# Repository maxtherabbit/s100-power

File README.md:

# s100-power
PCB for S100 Power Supply which fits both original Altair and Clone cabinets

Based on circuit designed by Gifford Toole. Provides 10A (with Hammond 167S12) or 20A (with Hammond 167V12) total current. Mounting provisions for both original Altair cabinet as well as clone cabniet designed by Mike Douglas.
My clone cabinet was purchased from https://adwaterandstir.com/ in 2024 and uses M4 hardware. The original one sold by Mike might use 6-32 instead. Make sure you check this before ordering the standoffs!
For the one using M4, I included appropriate length standoffs in the BOM. The M4 ones attach to the screws which connect the rear panel to the bottom panel. Get longer M4 screws and thread them into the existing welded screw bosses from the bottom, then attach standoffs to them. Affix the longer 4-40 standoffs to the front of the PCB with 4-40 screws, then bolt PCB to M4 standoffs with the original M4 screws which came with the cabniet.

I found that the Hammond 167S12 transformer fit the two pre-drilled holes in the rear panel, on the right side. You will need to drill two additional holes above the pre-drilled ones at the same width apart to secure the transformer properly.

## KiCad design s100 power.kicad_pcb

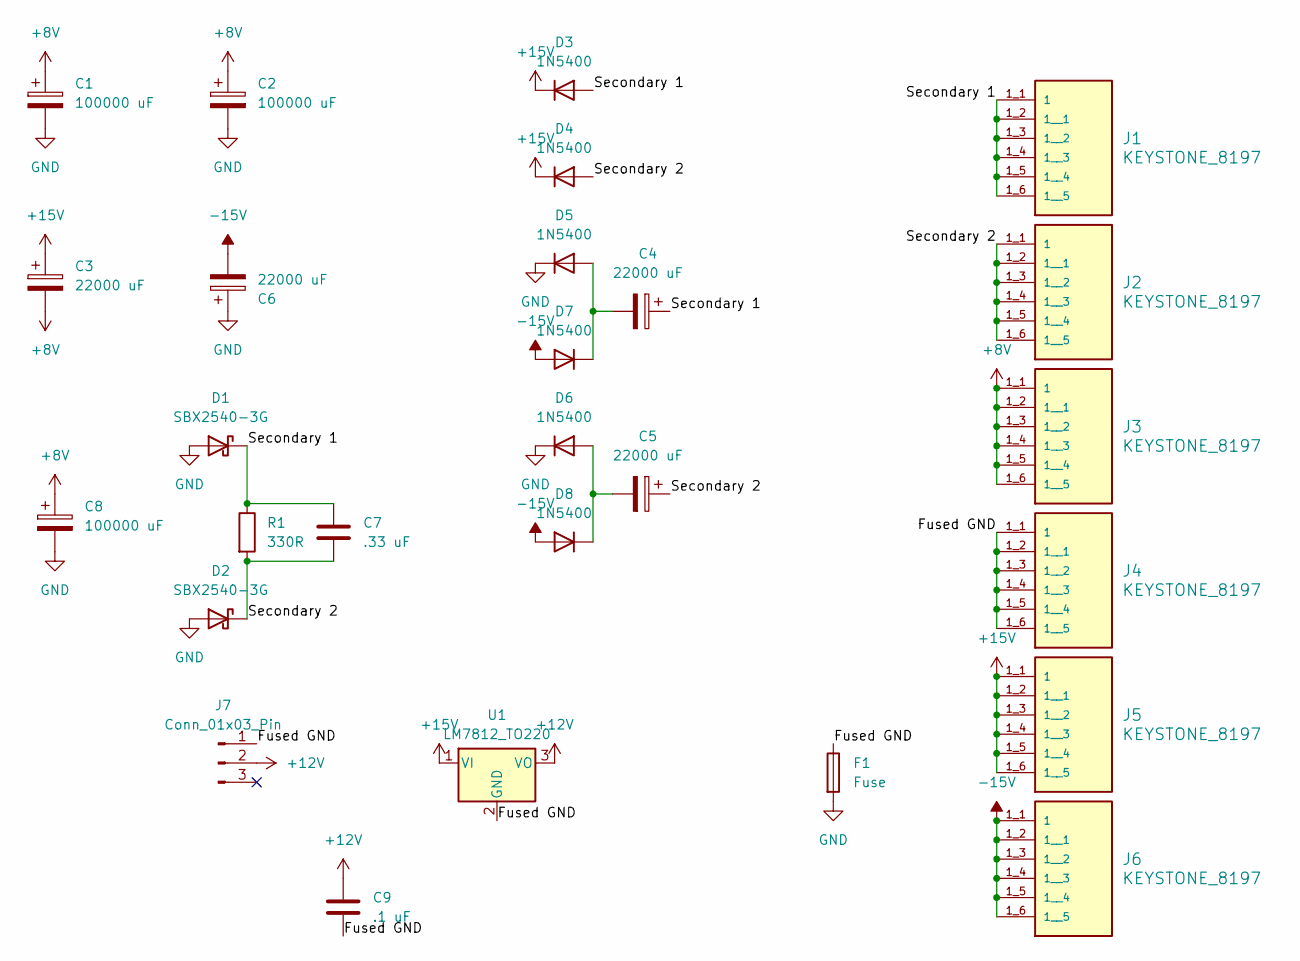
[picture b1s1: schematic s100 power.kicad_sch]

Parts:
C1, C2, C8: 100000 uF; CP_Radial_D35.0mm_P10.00mm_SnapIn
C3, C4, C5, C6: 22000 uF; CP_Radial_D25.0mm_P10.00mm_SnapIn
C7: .33 uF; C_Disc_D5.1mm_W3.2mm_P5.00mm
C9: .1 uF; C_Disc_D5.1mm_W3.2mm_P5.00mm
D1, D2: SBX2540-3G; D_DO-201AD_P15.24mm_Horizontal
D3, D4, D5, D6, D7, D8: 1N5400; D_DO-201AD_P15.24mm_Horizontal
F1: Fuse; Fuseholder_Clip-6.3x32mm_Littelfuse_122_Inline_P34.21x7.62m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
J1, J2, J3, J4, J5, J6: KEYSTONE_8197; PARTREV C
J7: Conn_01x03_Pin; Molex_KK-254_AE-6410-03A_1x03_P2.54mm_Vertical
R1: 330R; R_Axial_DIN0411_L9.9mm_D3.6mm_P15.24mm_Horizontal
U1: LM7812_TO220; TO-220-3_Vertical

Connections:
+8V: C1.1, C2.1, C3.2, C8.1, J3.1_1 (1), J3.1_2 (1__1), J3.1_3 (1__2), J3.1_4 (1__3), J3.1_5 (1__4), J3.1_6 (1__5)
+12V: C9.1, J7.2, U1.3 (VO)
+15V: C3.1, D3.1 (K), D4.1 (K), J5.1_1 (1), J5.1_2 (1__1), J5.1_3 (1__2), J5.1_4 (1__3), J5.1_5 (1__4), J5.1_6 (1__5), U1.1 (VI)
-15V: C6.2, D7.2 (A), D8.2 (A), J6.1_1 (1), J6.1_2 (1__1), J6.1_3 (1__2), J6.1_4 (1__3), J6.1_5 (1__4), J6.1_6 (1__5)
/Fused GND: C9.2, F1.1, J4.1_1 (1), J4.1_2 (1__1), J4.1_3 (1__2), J4.1_4 (1__3), J4.1_5 (1__4), J4.1_6 (1__5), J7.1, U1.2 (GND)
/Secondary 1: C4.1, C7.1, D1.1 (K), D3.2 (A), J1.1_1 (1), J1.1_2 (1__1), J1.1_3 (1__2), J1.1_4 (1__3), J1.1_5 (1__4), J1.1_6 (1__5), R1.1
/Secondary 2: C5.1, C7.2, D2.1 (K), D4.2 (A), J2.1_1 (1), J2.1_2 (1__1), J2.1_3 (1__2), J2.1_4 (1__3), J2.1_5 (1__4), J2.1_6 (1__5), R1.2
GND: C1.2, C2.2, C6.1, C8.2, D1.2 (A), D2.2 (A), D5.1 (K), D6.1 (K), F1.2
unnamed: C4.2, D5.2 (A), D7.1 (K)
unnamed: C5.2, D6.2 (A), D8.1 (K)

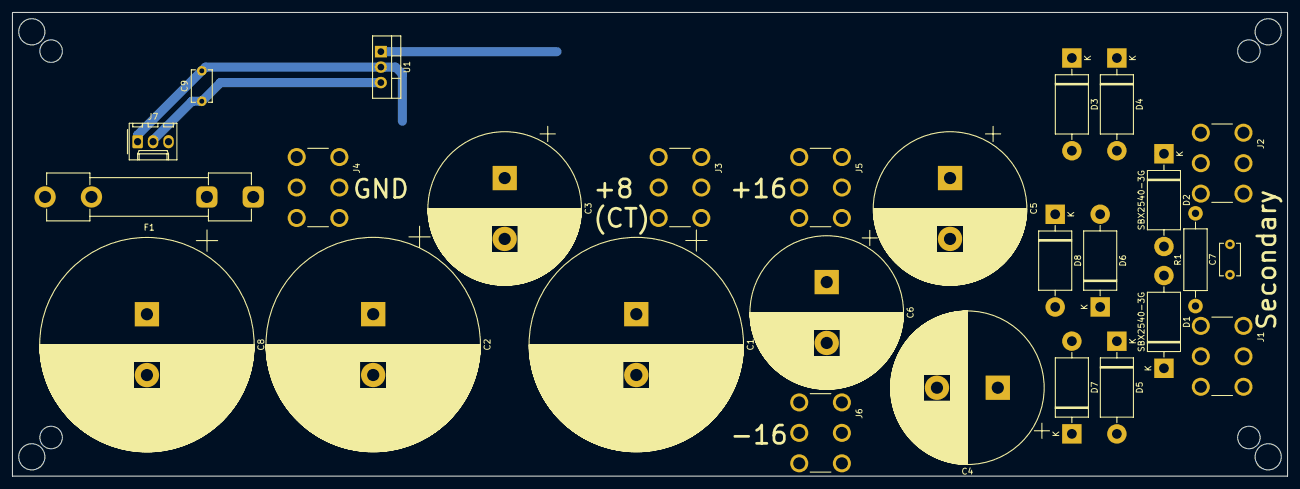
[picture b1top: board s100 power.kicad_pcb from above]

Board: 2 copper layers, 209.6 x 76.2 mm, 27 parts (0 on the bottom side), 10 nets.

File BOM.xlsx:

Reference | Quantity | Type/Value | Digikey Part | Vendor Part | Notes
C1, C2, C8 | 3 | CAP ALUM 100000UF 20% 16V SNAP | 565-ESMH160VNN104MA80U-ND | ESMH160VNN104MA80U | C8 is optional
C3-C6 | 4 | CAP ALUM 22000UF 20% 25V SNAP TH | 493-7259-ND | LLS1E223MELA
D1-D2 | 2 | DIODE SCHOTTKY 40V 25A AXIAL | 4878-SBX2540-3GCT-ND | SBX2540-3G
D3-D8 | 6 | 1N5400 or equivalent
C7 | 1 | CAP CER 0.33UF 50V X7R RADIAL | 445-173379-1-ND | FG24X7R1H334KNT06
R1 | 1 | 330 ohm 1/2 Watt Resistor
F1 | 2 | FUSE CLIP FOR 1/4" DIA. FUSE | 36-3500-ND | 3500
J1-J6 | 6 | TERM SCREW 6-32 6 PIN PCB | 36-8197-ND | 8197
J7 | 1 | CONN HEADER VERT 3POS 2.54MM | WM4112-ND | 22272031 | Optional for cooling fan
C9 | 1 | CAP CER 0.1UF 50V X7R RADIAL | 445-FK28X7R1H104KN000-ND | FK28X7R1H104KN000 | Optional for cooling fan
U1 | 1 | 7812 Linear Regulator |  |  | Optional for cooling fan
N/A | 2 | HEX SPACER M4 STEEL 12MM | 732-10555-ND | 970120471 | For mounting in Altair Clone cab attach to existing screw bosses on rear panel 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
N/A | 2 | 1/4 HEX X 5/8 LENGTH | 1772-2618-ND | 2106-440-AL-6 | For mounting in Altair Clone cab attach these to front of PCB with 4-40 screws
T1 | 1 | 12.6V CT, 115 VAC, 60 Hz Transformer |  | Hammond 167V12 or 167S12 | Recommend 167S12 (10A) for easier mounting in Altair Clone cabinet

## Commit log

2025-03-21 Update README.md
    Fix screw size
